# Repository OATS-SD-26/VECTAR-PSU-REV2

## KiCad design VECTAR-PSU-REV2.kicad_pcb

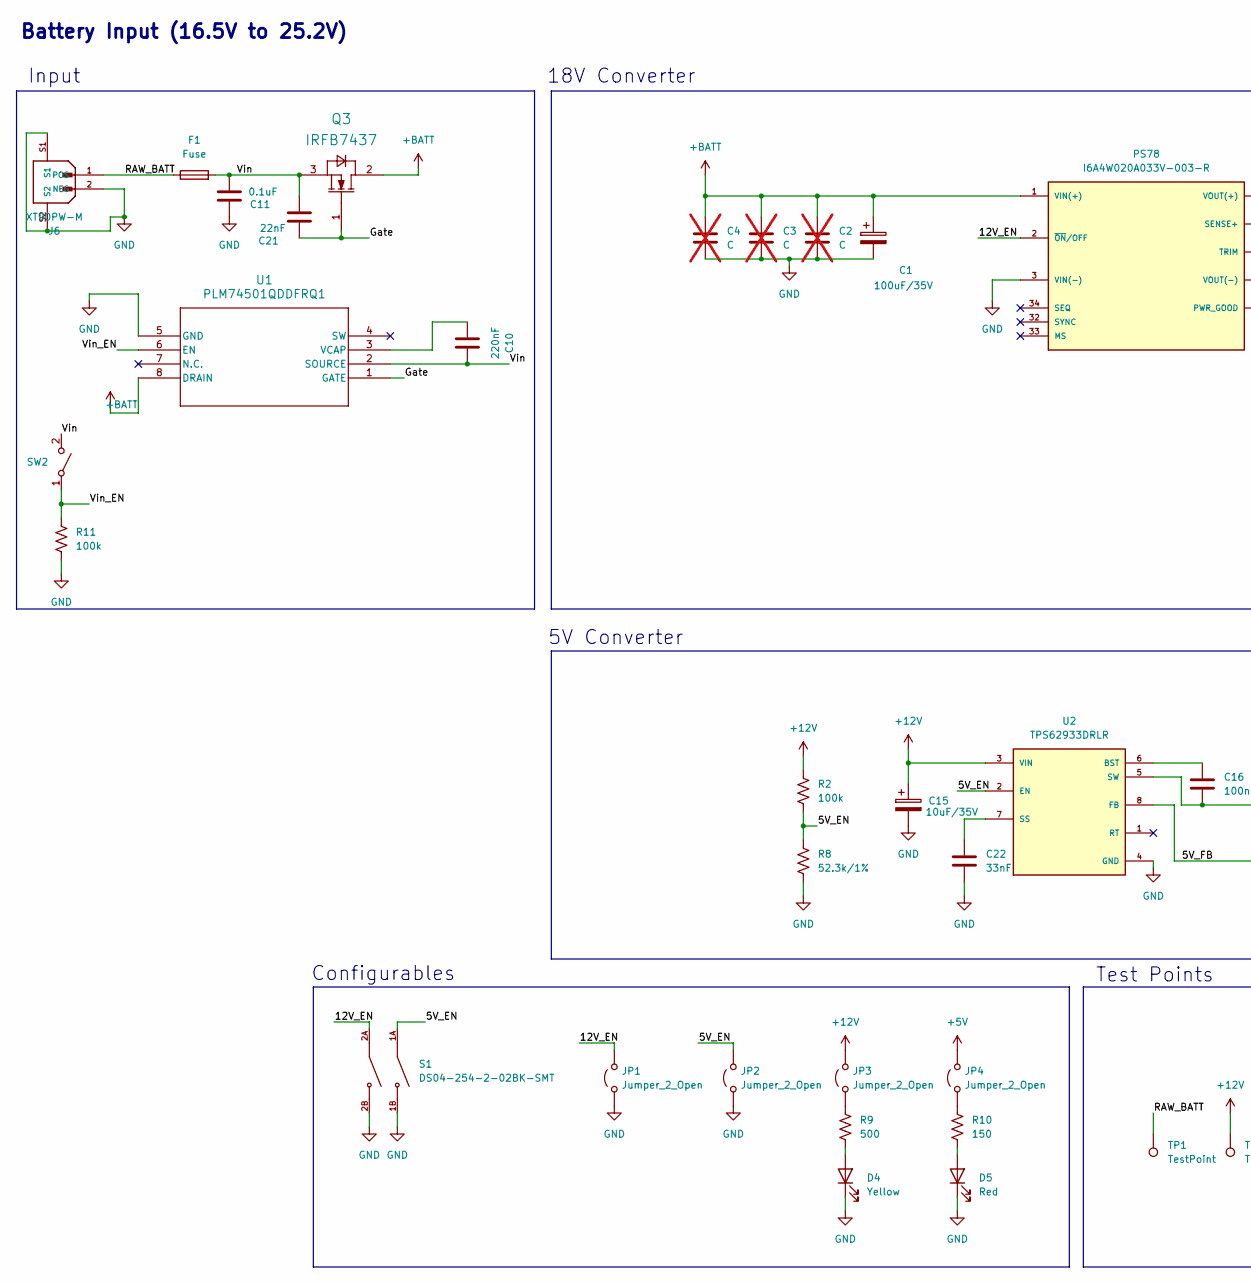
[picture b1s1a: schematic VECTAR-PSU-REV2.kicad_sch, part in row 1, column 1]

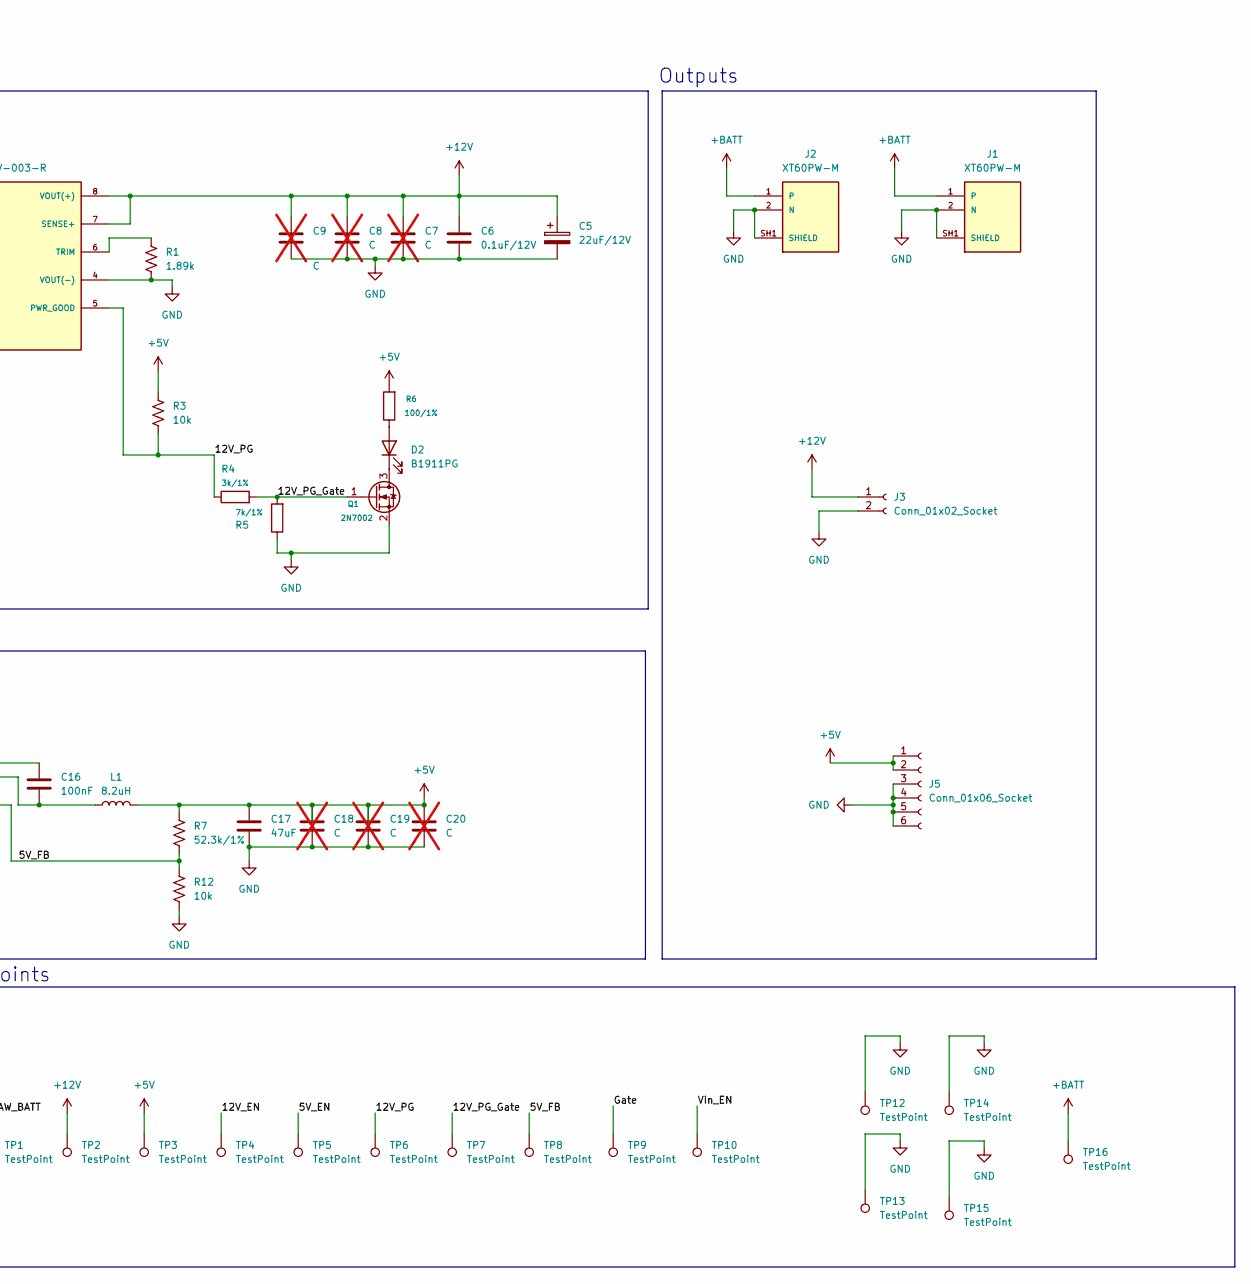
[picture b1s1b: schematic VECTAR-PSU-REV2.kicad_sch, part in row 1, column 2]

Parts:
C1: 100uF/35V; EHBSA035M1010608T
C2, C3, C4, C7, C8, C9, C18, C19, C20: C; C_0603_1608Metric; not fitted
C5: 22uF/12V; C_0805_2012Metric
C6: 0.1uF/12V; C_0603_1608Metric
C10: 220nF; C_0603_1608Metric
C11: 0.1uF; C_0603_1608Metric
C15: 10uF/35V; C_0603_1608Metric
C16: 100nF; C_0603_1608Metric
C17: 47uF; CAPAE660X600N
C21: 22nF; C_0603_1608Metric
C22: 33nF; C_0603_1608Metric
D2: B1911PG; LED_B1911PG--20D000514U1930_HVK
D4: Yellow; LTST_C190KSKT
D5: Red; LTST_S270KRKT
F1: Fuse; 3-140-178
J1, J2: XT60PW-M; AMASS_XT60PW-M; PARTREV 1.2
J3: Conn_01x02_Socket; Rocker-Switch
J5: Conn_01x06_Socket; 6-pin-connector
J6: XT90PW-M; AMASS_XT90PW-M; PARTREV V00
JP1, JP2, JP3, JP4: Jumper_2_Open; R_0603_1608Metric
L1: 8.2uH; IND_BOURNS_SRP1270
PS78: I6A4W020A033V-003-R; CONV_I6A4W020A033V-003-R; PARTREV V4; DigiKey_Part_Number 285-2669-ND
Q1: 2N7002; SOT95P240X111-3N
Q3: IRFB7437; TO254P483X1016X1944-3B
R1: 1.89k; R_0805_2012Metric
R2, R11: 100k; R_0603_1608Metric
R3, R12: 10k; R_0603_1608Metric
R4: 3k/1%; R_0603_1608Metric
R5: 7k/1%; R_0603_1608Metric
R6: 100/1%; R_0603_1608Metric
R7, R8: 52.3k/1%; R_0603_1608Metric
R9: 500; R_0603_1608Metric
R10: 150; R_0603_1608Metric
S1: DS04-254-2-02BK-SMT; SW_DS04-254-2-02BK-SMT; PARTREV V0.0
SW2: RA1113112R; Rocker-Switch
TP1, TP2, TP3, TP4, TP5, TP6, TP7, TP8, TP9, TP10, TP12, TP13, TP14, TP15, TP16: TestPoint; KEYSTONE_5002
U1: PLM74501QDDFRQ1; PLM74501QDDFRQ1_TEX
U2: TPS62933DRLR; SOTFL50P160X60-8N; PARTREV D; DigiKey_Part_Number 296-TPS62933DRLRCT-ND

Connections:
+5V: C17.1, C18.1, C19.1, C20.1, J5.1, J5.2, JP4.2 (B), L1.2, R3.1, R6.2, R7.1, TP3.1
+12V: C5.1, C6.1, C7.1, C8.1, C9.1, C15.1, J3.1, JP3.2 (B), PS78.7 (SENSE+), PS78.8 (VOUT(+)), R2.1, TP2.1, U2.3 (VIN)
+BATT: C1.1, C2.1, C3.1, C4.1, J1.1, J2.1, PS78.1 (VIN(+)), Q3.2 (DRAIN), TP16.1, U1.8 (DRAIN)
/5V_EN: JP2.2 (B), R2.2, R8.1, S1.1A, TP5.1, U2.2 (EN)
/5V_FB: R7.2, R12.1, TP8.1, U2.8 (FB)
/12V_EN: JP1.2 (B), PS78.2 (~ON/OFF), S1.2A, TP4.1
/12V_PG: PS78.5 (PWR_GOOD), R3.2, R4.1, TP6.1
/12V_PG_Gate: Q1.1 (G), R4.2, R5.2, TP7.1
/Gate: C21.1, Q3.1 (GATE), TP9.1, U1.1 (GATE)
/RAW_BATT: F1.1, J6.1 (POS), TP1.1
/Vin: C10.1, C11.2, C21.2, F1.2, Q3.3 (SOURCE), SW2.2 (B), U1.2 (SOURCE)
/Vin_EN: R11.1, SW2.1 (A), TP10.1, U1.6 (EN)
GND: C1.2, C2.2, C3.2, C4.2, C5.2, C6.2, C7.2, C8.2, C9.2, C11.1, C15.2, C17.2, C18.2, C19.2, C20.2, C22.2, D4.1 (K), D5.1 (K), J1.2 (N), J1.SH1 (SHIELD), J1.SH2 (SHIELD), J2.2 (N), J2.SH1 (SHIELD), J2.SH2 (SHIELD), J3.2, J5.3, J5.4, J5.5, J5.6, J6.2 (NEG), J6.S1, J6.S2, JP1.1 (A), JP2.1 (A), PS78.3 (VIN(-)), PS78.4 (VOUT(-)), Q1.2 (S), R1.2, R5.1, R8.2, R11.2, R12.2, S1.1B, S1.2B, TP12.1, TP13.1, TP14.1, TP15.1, U1.5 (GND), U2.4 (GND)
unnamed: D2.2 (A), R6.1
unnamed: D2.1 (K), Q1.3 (D)
unnamed: D4.2 (A), R9.2
unnamed: D5.2 (A), R10.2
unnamed: JP3.1 (A), R9.1
unnamed: JP4.1 (A), R10.1
unnamed: PS78.6 (TRIM), R1.1
unnamed: C10.2, U1.3 (VCAP)
unnamed: C16.1, U2.6 (BST)
unnamed: C22.1, U2.7 (SS)
unnamed: C16.2, L1.1, U2.5 (SW)

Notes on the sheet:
Input
Battery Input (16.5V to 25.2V)
Test Points
18V Converter
Outputs
5V Converter
Configurables

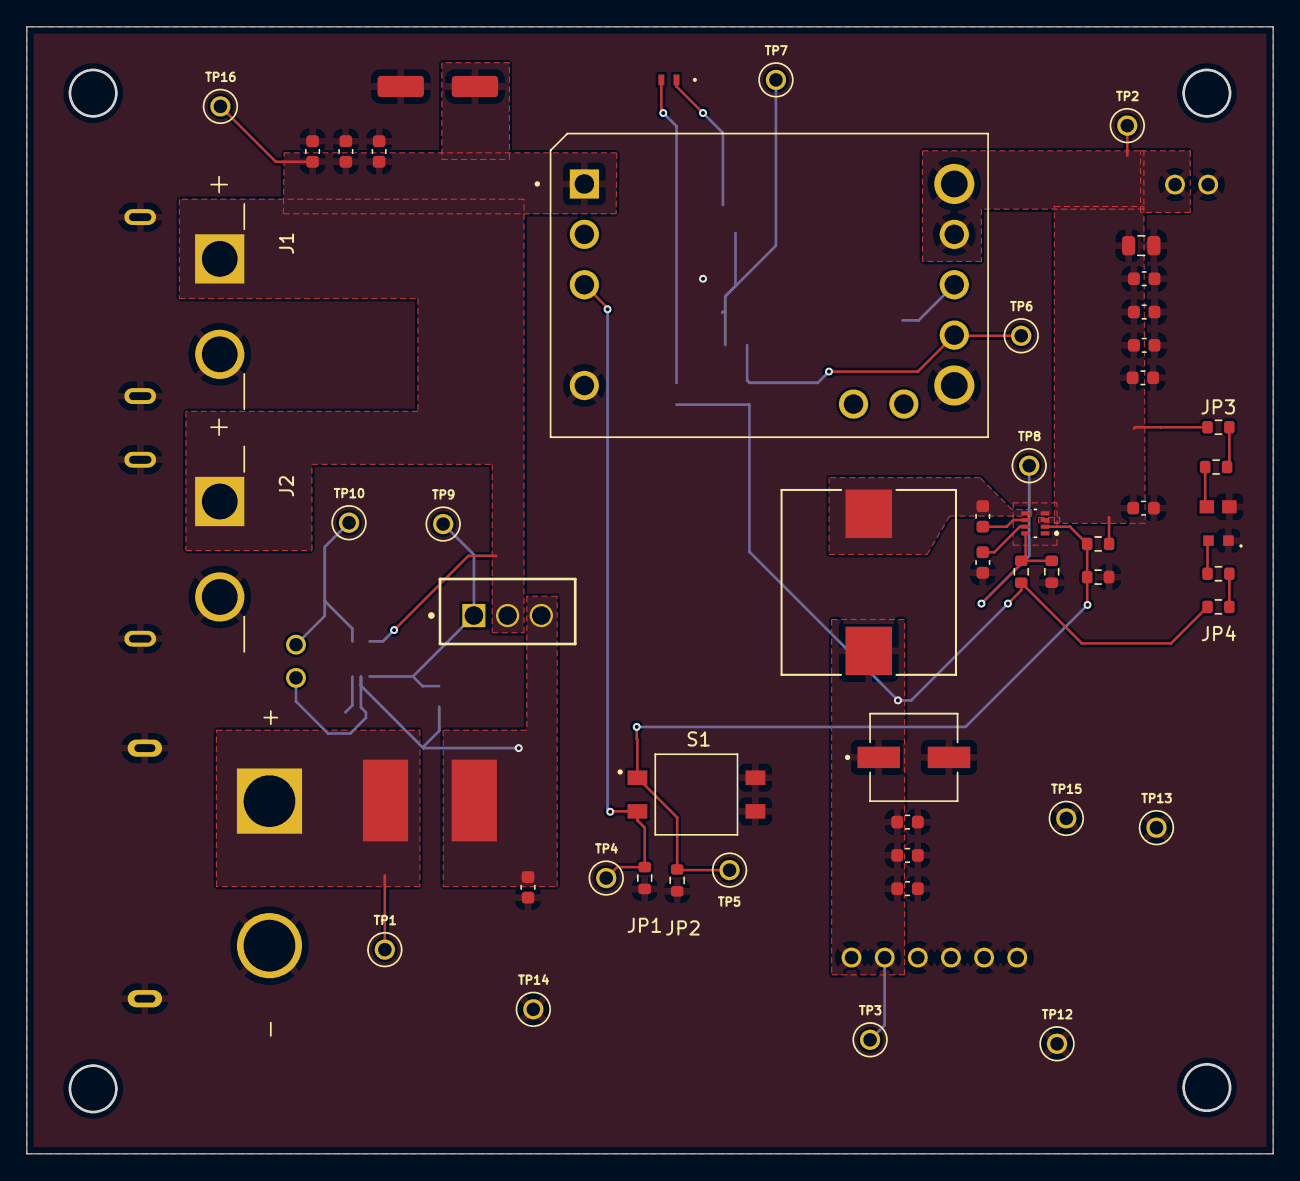
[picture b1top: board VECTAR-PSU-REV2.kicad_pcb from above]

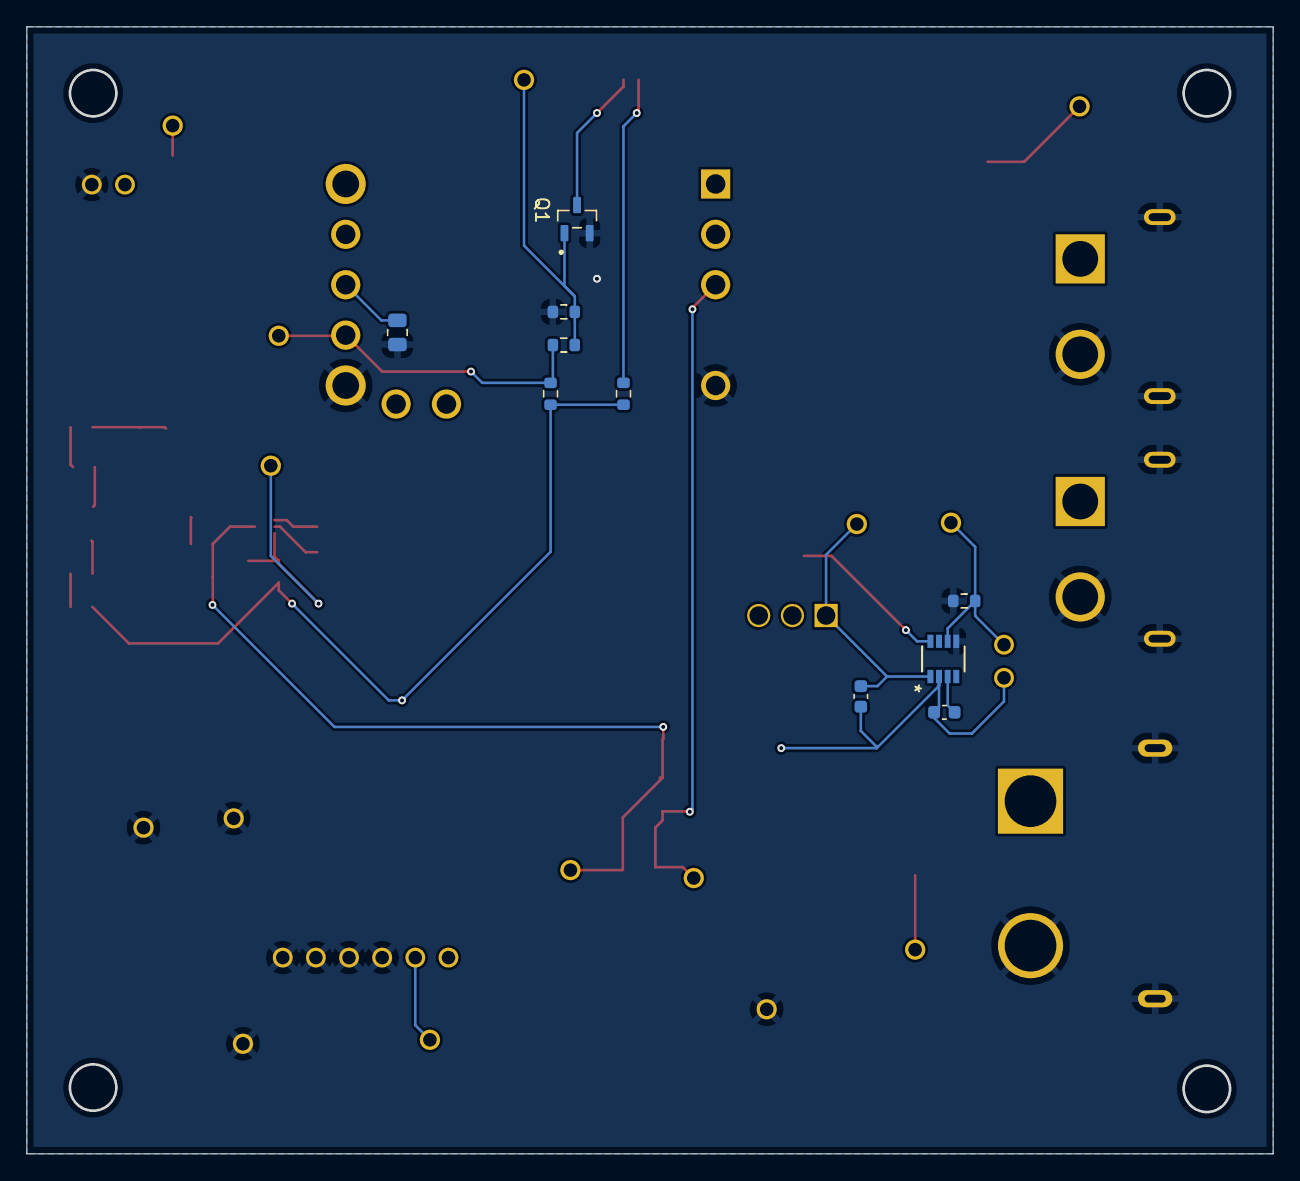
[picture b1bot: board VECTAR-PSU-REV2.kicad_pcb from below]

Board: 2 copper layers, 93.9 x 84.9 mm, 67 parts (10 on the bottom side), 24 nets.

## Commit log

2026-04-02 Copy rev1 materials
2026-04-04 Starting to sim
2026-04-07 Rev 2 complete - PCB and components ordered
2026-04-28 Version that was manufactured
2026-05-01 final commit
